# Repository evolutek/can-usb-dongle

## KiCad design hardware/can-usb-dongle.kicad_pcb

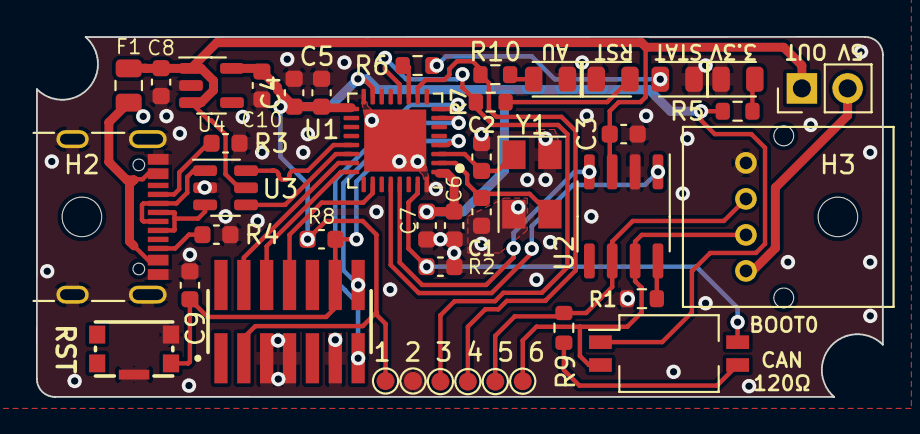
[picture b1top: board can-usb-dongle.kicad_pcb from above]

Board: 2 copper layers, 47.0 x 20.0 mm, 45 parts (1 on the bottom side), 33 nets.

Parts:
C1, C2: 18pF; C_0603_1608Metric
C3, C5, C6, C9: 100nF; C_0603_1608Metric
C4: 10uF; C_0603_1608Metric
C7: 10nF; C_0603_1608Metric
C8, C10: 1uF; C_0603_1608Metric
D1: RED; LED_0805_2012Metric
D2: GREEN; LED_0805_2012Metric
D3, D4: ORANGE; LED_0805_2012Metric
F1: 0805; C_0805_2012Metric
G1: Logo; logo-evo-min
H2, H3: M2; MountingHole_2.2mm_M2_ISO14580
J1: USB C - 2.0; USB_C_Receptacle_GCT_USB4105-xx-A_16P_TopMnt_Horizontal
J2: Conn_01x04_Pin; S04B-PASK
J3: STLINK; SAMTEC_FTSH-107-01-L-DV-K
JP1: Power selector; PinHeader_1x02_P2.54mm_Vertical
R1: 0; R_0603_1608Metric
R2, R8: 10k; C_0603_1608Metric
R3, R4: 5k1; C_0603_1608Metric
R5, R6, R7, R10: 510; R_0603_1608Metric
R9: 120; R_0603_1608Metric
SW1: 435431019840
SW2: 416131160802; SW_DIP_SPSTx02_Slide_KingTek_DSHP02TS_W7.62mm_P1.27mm
TP1, TP2, TP3, TP4, TP5, TP6: TestPoint_Small; TestPoint_Pad_D1.0mm
U1: STM32G491KEUx; QFN-32-1EP_5x5mm_P0.5mm_EP3.45x3.45mm
U2: MCP2551-I-SN; SOIC-8_3.9x4.9mm_P1.27mm
U3: WE-TVS-82400102; SOT-23-6
U4: NCP718xSN330; SOT-23-5
Y1: 16MHz; Crystal_SMD_5032-4Pin_5.0x3.2mm

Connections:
+3.3V: C4.1, C5.1, C6.1, C7.1, C10.1, J3.3, R5.2, R8.2, SW2.1, TP1.1, U1.1 (VDD), U1.15 (VDDA), U1.17 (VDD), U4.5 (OUT)
+5V: C3.1, C8.1, F1.2, JP1.1 (A), U2.3 (VDD), U3.5, U4.1 (IN), U4.3 (EN)
/BOOT0: R2.2, SW2.4, U1.31 (PB8)
/CANH: J2.2, SW2.2, TP6.1, U2.7 (CANH)
/CANL: J2.3, R9.1, TP5.1, U2.6 (CANL)
/CAN_RX: U1.29 (PB6), U2.4 (RXD)
/CAN_TX: U1.28 (PB5), U2.1 (TXD)
/D_N: J1.A7 (D-), J1.B7 (D-), U3.1
/D_P: J1.A6 (D+), J1.B6 (D+), U3.3
/EXT_AU: R10.2, TP4.1, U1.10 (PA5)
/EXT_RST: R7.2, TP3.1, U1.12 (PA7)
/STATUS: R6.2, U1.11 (PA6)
/SWCLK: J3.6, U1.24 (PA14)
/SWDIO: J3.4, U1.23 (PA13)
/SWO: J3.8, U1.26 (PB3)
/USB_N: U1.21 (PA11), U3.6
/USB_P: U1.22 (PA12), U3.4
/VCP_RX: J3.13, U1.8 (PA3)
/VCP_TX: J3.14, U1.7 (PA2)
/~RST: C9.1, J3.12, R8.1, SW1.4, U1.4 (PG10)
GND: C1.2, C2.2, C3.2, C4.2, C5.2, C6.2, C7.2, C8.2, C9.2, C10.2, D1.1 (K), D2.1 (K), D3.1 (K), D4.1 (K), J1.A1 (GND), J1.A12 (GND), J1.B1 (GND), J1.B12 (GND), J1.S1 (SHIELD), J2.4, J3.5, J3.7, J3.11, R1.2, R2.1, R3.2, R4.1, SW1.3, SW1.SH, TP2.1, U1.14 (VSSA), U1.16 (VSS), U1.32 (VSS), U1.33 (VSS), U2.2 (VSS), U3.2, U4.2 (GND), Y1.2, Y1.4
unnamed: D1.2 (A), R5.1
unnamed: D2.2 (A), R6.1
unnamed: D3.2 (A), R7.1
unnamed: D4.2 (A), R10.1
unnamed: F1.1, J1.A4 (VBUS), J1.A9 (VBUS), J1.B4 (VBUS), J1.B9 (VBUS)
unnamed: J1.A5 (CC1), R3.1
unnamed: J1.B5 (CC2), R4.2
unnamed: J2.1, JP1.2 (B)
unnamed: R9.2, SW2.3
unnamed: C1.1, U1.2 (PF0), Y1.3
unnamed: C2.1, U1.3 (PF1), Y1.1
unnamed: R1.1, U2.8 (Rs)

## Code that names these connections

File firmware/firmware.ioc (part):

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Mcu.Name=STM32G491K(C-E)Ux
Mcu.Package=UFQFPN32
Mcu.UserName=STM32G491KEUx
PA11.GPIOParameters=GPIO_Label
PA11.GPIO_Label=USB D-
PA11.Mode=Device
PA11.Signal=USB_DM
PA12.GPIOParameters=GPIO_Label
PA12.GPIO_Label=USB D+
PA12.Mode=Device
PA12.Signal=USB_DP
PA13.GPIOParameters=GPIO_Label
PA13.GPIO_Label=SWDIO
PA13.Mode=Trace_Asynchronous_SW
PA13.Signal=SYS_JTMS-SWDIO
PA14.GPIOParameters=GPIO_Label
PA14.GPIO_Label=SWCLK 
PA14.Mode=Trace_Asynchronous_SW
PA14.Signal=SYS_JTCK-SWCLK
PA2.GPIOParameters=GPIO_Label
PA2.GPIO_Label=VCP_TX
PA2.Mode=Asynchronous
PA2.Signal=USART2_TX
PA3.GPIOParameters=GPIO_Label
PA3.GPIO_Label=VCP_RX
PA3.Mode=Asynchronous
PA3.Signal=USART2_RX
PA5.GPIOParameters=GPIO_Label
PA5.GPIO_Label=AU_EXT
PA5.Signal=GPIO_Output
PA6.GPIOParameters=GPIO_Label
PA6.GPIO_Label=STATUS
PA6.Signal=GPIO_Output
PA7.GPIOParameters=GPIO_Label
PA7.GPIO_Label=RST_EXT
PA7.Signal=GPIO_Output
PB3.GPIOParameters=GPIO_Label
PB3.GPIO_Label=SWO
PB3.Mode=Trace_Asynchronous_SW
PB3.Signal=SYS_JTDO-SWO
PB5.GPIOParameters=GPIO_Label
PB5.GPIO_Label=CAN RX 
PB5.Mode=FDCAN_Activate
PB5.Signal=FDCAN2_RX
PB6.GPIOParameters=GPIO_Label
PB6.GPIO_Label=CAN TX
PB6.Mode=FDCAN_Activate
PB6.Signal=FDCAN2_TX
RCC.HSE_VALUE=8000000
RCC.SYSCLKFreq_VALUE=16000000
board=custom

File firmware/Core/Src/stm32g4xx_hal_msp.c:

/* USER CODE BEGIN Header */
/**
  ******************************************************************************
  * @file         stm32g4xx_hal_msp.c
  * @brief        This file provides code for the MSP Initialization
  *               and de-Initialization codes.
  ******************************************************************************
  * @attention
  *
  * Copyright (c) 2024 STMicroelectronics.
  * All rights reserved.
  *
  * This software is licensed under terms that can be found in the LICENSE file
  * in the root directory of this software component.
  * If no LICENSE file comes with this software, it is provided AS-IS.
  *
  ******************************************************************************
  */
/* USER CODE END Header */

/* Includes ------------------------------------------------------------------*/
#include "main.h"

/* USER CODE BEGIN Includes */

/* USER CODE END Includes */

/* Private typedef -----------------------------------------------------------*/
/* USER CODE BEGIN TD */

/* USER CODE END TD */

/* Private define ------------------------------------------------------------*/
/* USER CODE BEGIN Define */

/* USER CODE END Define */

/* Private macro -------------------------------------------------------------*/
/* USER CODE BEGIN Macro */

/* USER CODE END Macro */

/* Private variables ---------------------------------------------------------*/
/* USER CODE BEGIN PV */

/* USER CODE END PV */

/* Private function prototypes -----------------------------------------------*/
/* USER CODE BEGIN PFP */

/* USER CODE END PFP */

/* External functions --------------------------------------------------------*/
/* USER CODE BEGIN ExternalFunctions */

/* USER CODE END ExternalFunctions */

/* USER CODE BEGIN 0 */

/* USER CODE END 0 */
/**
  * Initializes the Global MSP.
  */
void HAL_MspInit(void)
{
  /* USER CODE BEGIN MspInit 0 */

  /* USER CODE END MspInit 0 */

  __HAL_RCC_SYSCFG_CLK_ENABLE();
  __HAL_RCC_PWR_CLK_ENABLE();

  /* System interrupt init*/

  /** Disable the internal Pull-Up in Dead Battery pins of UCPD peripheral
  */
  HAL_PWREx_DisableUCPDDeadBattery();

  /* USER CODE BEGIN MspInit 1 */

  /* USER CODE END MspInit 1 */
}

/**
* @brief FDCAN MSP Initialization
* This function configures the hardware resources used in this example
* @param hfdcan: FDCAN handle pointer
* @retval None
*/
void HAL_FDCAN_MspInit(FDCAN_HandleTypeDef* hfdcan)
{
  GPIO_InitTypeDef GPIO_InitStruct = {0};
  RCC_PeriphCLKInitTypeDef PeriphClkInit = {0};
  if(hfdcan->Instance==FDCAN2)
  {
  /* USER CODE BEGIN FDCAN2_MspInit 0 */

  /* USER CODE END FDCAN2_MspInit 0 */

  /** Initializes the peripherals clocks
  */
    PeriphClkInit.PeriphClockSelection = RCC_PERIPHCLK_FDCAN;
    PeriphClkInit.FdcanClockSelection = RCC_FDCANCLKSOURCE_PCLK1;
    if (HAL_RCCEx_PeriphCLKConfig(&PeriphClkInit) != HAL_OK)
    {
      Error_Handler();
    }

    /* Peripheral clock enable */
    __HAL_RCC_FDCAN_CLK_ENABLE();

    __HAL_RCC_GPIOB_CLK_ENABLE();
    /**FDCAN2 GPIO Configuration
    PB5     ------> FDCAN2_RX
    PB6     ------> FDCAN2_TX
    */
    GPIO_InitStruct.Pin = CAN_RX_Pin|CAN_TX_Pin;
    GPIO_InitStruct.Mode = GPIO_MODE_AF_PP;
    GPIO_InitStruct.Pull = GPIO_NOPULL;
    GPIO_InitStruct.Speed = GPIO_SPEED_FREQ_LOW;
    GPIO_InitStruct.Alternate = GPIO_AF9_FDCAN2;
    HAL_GPIO_Init(GPIOB, &GPIO_InitStruct);

  /* USER CODE BEGIN FDCAN2_MspInit 1 */

  /* USER CODE END FDCAN2_MspInit 1 */
  }

}

/**
* @brief FDCAN MSP De-Initialization
* This function freeze the hardware resources used in this example
* @param hfdcan: FDCAN handle pointer
* @retval None
*/
void HAL_FDCAN_MspDeInit(FDCAN_HandleTypeDef* hfdcan)
{
  if(hfdcan->Instance==FDCAN2)
  {
  /* USER CODE BEGIN FDCAN2_MspDeInit 0 */

  /* USER CODE END FDCAN2_MspDeInit 0 */
    /* Peripheral clock disable */
    __HAL_RCC_FDCAN_CLK_DISABLE();

    /**FDCAN2 GPIO Configuration
    PB5     ------> FDCAN2_RX
    PB6     ------> FDCAN2_TX
    */
    HAL_GPIO_DeInit(GPIOB, CAN_RX_Pin|CAN_TX_Pin);

  /* USER CODE BEGIN FDCAN2_MspDeInit 1 */

  /* USER CODE END FDCAN2_MspDeInit 1 */
  }

}

/**
* @brief UART MSP Initialization
* This function configures the hardware resources used in this example
* @param huart: UART handle pointer
* @retval None
*/
void HAL_UART_MspInit(UART_HandleTypeDef* huart)
{
  GPIO_InitTypeDef GPIO_InitStruct = {0};
  RCC_PeriphCLKInitTypeDef PeriphClkInit = {0};
  if(huart->Instance==USART2)
  {
  /* USER CODE BEGIN USART2_MspInit 0 */

  /* USER CODE END USART2_MspInit 0 */

  /** Initializes the peripherals clocks
  */
    PeriphClkInit.PeriphClockSelection = RCC_PERIPHCLK_USART2;
    PeriphClkInit.Usart2ClockSelection = RCC_USART2CLKSOURCE_PCLK1;
    if (HAL_RCCEx_PeriphCLKConfig(&PeriphClkInit) != HAL_OK)
    {
      Error_Handler();
    }

    /* Peripheral clock enable */
    __HAL_RCC_USART2_CLK_ENABLE();

    __HAL_RCC_GPIOA_CLK_ENABLE();
    /**USART2 GPIO Configuration
    PA2     ------> USART2_TX
    PA3     ------> USART2_RX
    */
    GPIO_InitStruct.Pin = VCP_TX_Pin|VCP_RX_Pin;
    GPIO_InitStruct.Mode = GPIO_MODE_AF_PP;
    GPIO_InitStruct.Pull = GPIO_NOPULL;
    GPIO_InitStruct.Speed = GPIO_SPEED_FREQ_LOW;
    GPIO_InitStruct.Alternate = GPIO_AF7_USART2;
    HAL_GPIO_Init(GPIOA, &GPIO_InitStruct);

  /* USER CODE BEGIN USART2_MspInit 1 */

  /* USER CODE END USART2_MspInit 1 */
  }

}

/**
* @brief UART MSP De-Initialization
* This function freeze the hardware resources used in this example
* @param huart: UART handle pointer
* @retval None
*/
void HAL_UART_MspDeInit(UART_HandleTypeDef* huart)
{
  if(huart->Instance==USART2)
  {
  /* USER CODE BEGIN USART2_MspDeInit 0 */

  /* USER CODE END USART2_MspDeInit 0 */
    /* Peripheral clock disable */
    __HAL_RCC_USART2_CLK_DISABLE();

    /**USART2 GPIO Configuration
    PA2     ------> USART2_TX
    PA3     ------> USART2_RX
    */
    HAL_GPIO_DeInit(GPIOA, VCP_TX_Pin|VCP_RX_Pin);

  /* USER CODE BEGIN USART2_MspDeInit 1 */

  /* USER CODE END USART2_MspDeInit 1 */
  }

}

/**
* @brief PCD MSP Initialization
* This function configures the hardware resources used in this example
* @param hpcd: PCD handle pointer
* @retval None
*/
void HAL_PCD_MspInit(PCD_HandleTypeDef* hpcd)
{
  RCC_PeriphCLKInitTypeDef PeriphClkInit = {0};
  if(hpcd->Instance==USB)
  {
  /* USER CODE BEGIN USB_MspInit 0 */

  /* USER CODE END USB_MspInit 0 */

  /** Initializes the peripherals clocks
  */
    PeriphClkInit.PeriphClockSelection = RCC_PERIPHCLK_USB;
    PeriphClkInit.UsbClockSelection = RCC_USBCLKSOURCE_HSI48;
    if (HAL_RCCEx_PeriphCLKConfig(&PeriphClkInit) != HAL_OK)
    {
      Error_Handler();
    }

    /* Peripheral clock enable */
    __HAL_RCC_USB_CLK_ENABLE();
  /* USER CODE BEGIN USB_MspInit 1 */

  /* USER CODE END USB_MspInit 1 */
  }

}

/**
* @brief PCD MSP De-Initialization
* This function freeze the hardware resources used in this example
* @param hpcd: PCD handle pointer
* @retval None
*/
void HAL_PCD_MspDeInit(PCD_HandleTypeDef* hpcd)
{
  if(hpcd->Instance==USB)
  {
  /* USER CODE BEGIN USB_MspDeInit 0 */

  /* USER CODE END USB_MspDeInit 0 */
    /* Peripheral clock disable */
    __HAL_RCC_USB_CLK_DISABLE();
  /* USER CODE BEGIN USB_MspDeInit 1 */

  /* USER CODE END USB_MspDeInit 1 */
  }

}

/* USER CODE BEGIN 1 */

/* USER CODE END 1 */

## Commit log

2024-01-05 WIP Schematics
2024-01-05 initial schematic
2024-01-05 little crosses everywhere :)
2024-01-05 started routing
2024-01-05 cubemx
2024-01-06 board finalized
2024-01-06 minor fix
2024-01-06 Add base firmware
2024-01-06 CAN USB Dongle V1.0
2024-01-07 fixed the usb - c connector
2024-01-07 changed the usb footprint
2024-01-07 Fix gerber files
2024-01-08 reworked mounting solution
2025-05-25 add queue API to handle can/usb messages
2025-05-25 add config.h + begin CAN driver impl
2025-09-23 continue impl
2025-09-25 begin usb driver implem | TODO fix build errors + add can/usb conversions + define usb package format
2025-09-26 TODO format translation
2025-10-23 begin parsing
